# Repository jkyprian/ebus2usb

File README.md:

# ebus2usb - 1TE DIN Rail eBUS to USB Type-C Interface

eBUS is a serial 2-wire serial data-bus, often used in heating, solar energy, and other building automation systems. This project provides an interface to access an eBUS via USB.
It uses a series transistor regulator circuit with a low IZT zener diode to extract the operating voltage from the eBUS, an ADuM1201 for the galvanic isolation, and a STM32 microcontroller for the UART to USB conversion.
Power consumption on the eBUS side is between 475uA (eBUS low/8V) and 750uA (eBUS idle high/24V), making the interface qualify as a class 0 device with respect to the eBUS specification.
It has been designed to fit into an [CNMB/1/2](https://www.camdenboss.com/camden-boss/cnmb12-din-rail-module-box%2c-polycarbonate-enclosure%2c-industrial-iot-electronics-housing/c-23/p-18541) 1TE DIN rail enclosure by CAMDENBOSS. The interface is intended to be used with [ebusd](https://github.com/john30/ebusd/). Note that the firmware is currently just a proof-of-concept and only implements a basic uart to USB bridge. Support for the ebusd enhanced protocol is planned for the near future.

## Schematic

## PCB Layout

When ordering at JLCPCB, remove the mouse bites and cut the boards yourself. Otherwise JLCPCB will charge you for two designs.

## BOM

|Designator|Footprint|Quantity|Value|LCSC Part #
|:---|:---|:---|:---|:---
|C1, C2, C7|C0805|3|10u|C15850
|C10, C3, C4, C5, C6, C8, C9|C0603|7|100n|C14663
|C11, C12|C0805|2|1u|C28323
|D1, D2, D4|SOT-23-3|3|BAV99|C2500
|D3|SOD-123|1|5V6, Onsemi MMSZ4690*|C152307
|D5|SOD-123|1|24V/1W, KDZVTR24B, MM1W24|C209605, C438336
|D6|SOD-123|1|7V5/1W, KDZVTR7.5B, MM1W7V5|C209594, C382950
|D7|LED_0603|1|LED|C72043
|D8, D9, D10|D3.0mm|3|3mm LED|[CHANZON 3mm diffused LED](https://www.aliexpress.com/item/1936229691.html)
|J1|MSTBA_2,5_2-G-5,08|1|MSTBA 2,5/2-G-5,08|C3697
|J2, J6|Molex_PicoBlade_53047-0210|2|Molex 53047-0210|C114130
|J3, J7|Molex_PicoBlade_53047-0410|2|Molex 53047-0410|C504989
|J4|TC2030-NL|1|Tag-Connect 6-Pin \"No Legs\" TC2030-NL Plug-of-Nails|[TC2030-CTX-NL-STDC14](https://www.tag-connect.com/product/tc2030-ctx-nl-stdc14-for-use-with-stm32-processors-with-stlink-v3)
|J5|HRO_TYPE-C-31-M-12|1|HRO TYPE-C-31-M-12|C165948
|J8|PinHeader_1x02_P1.27mm|1|Harwin M50-3530242|C2881948
|Q1, Q2|SOT-23-3|2|BC817-40, S9013J3|C52801, C6749
|R1, R2, R3|R0603|3|100K|C25803
|R10|R0603|1|47K|C25819
|R12, R13|R0603|2|5K1|C23186
|R14|R0805|1|100K|C149504
|R15, R16|R0805|2|15K|C17475
|R4|R0603|1|4K7|C23162
|R5|R0603|1|300K|C23024
|R6|R0603|1|51K|C23196
|R7|R0603|1|2M|C22976
|R8|R0603|1|10K|C25804
|R9|R0603|1|0R|C21189
|U1|SO08|1|AZV3002, TSX3702|C5123396, C2970396
|U2|SO08|1|ADuM1201, π122U31|C9669, C471590
|U5|SOT-23-6L|1|SRV05-4|C85364
|U6|SOT-23-3|1|XC6206P332MR|C5446
|U7|LQFP-32|1|STM32L412KBT6, STM32F042K6T6|C529438, C69216

\* Low IZT of 50uA is required. Other manufacturers than Onsemi may not qualify. For example, MMSZ4690 from Jiangsu Changjing Elec. Tech. is not recommened.

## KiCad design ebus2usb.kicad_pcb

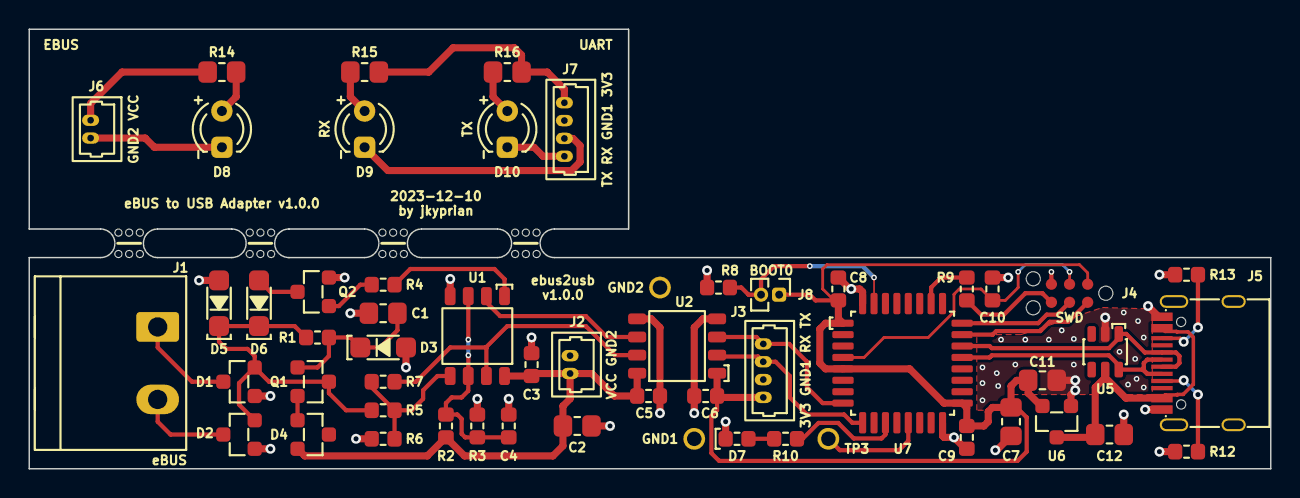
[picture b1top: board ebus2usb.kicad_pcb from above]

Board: 2 copper layers, 87.0 x 30.8 mm, 59 parts (0 on the bottom side), 40 nets.

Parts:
C1, C2, C7: 10u; C0805
C3, C4, C5, C6, C8, C9, C10: 100n; C0603
C11, C12: 1u; C0805
D1, D2, D4: BAV99; SOT-23-3
D3: 5V6; SOD-123
D5: 24V/1W; SOD-123
D6: 7V5/1W; SOD-123
D7: LED; LED_0603
D8, D9, D10: LED; LED_D3.0mm
J1: MSTBA 2,5/2-G-5,08; MSTBA_2,5_2-G-5,08
J2, J6: Molex 53047-0210; Molex_PicoBlade_53047-0210
J3, J7: Molex 53047-0410; Molex_PicoBlade_53047-0410
J4: TC2030; TC-2030NL
J5: HRO TYPE-C-31-M-12; HRO_TYPE-C-31-M-12
J8: Harwin M50-3530242; PinHeader_1x02_P1.27mm
Q1, Q2: BC817-40; SOT-23-3
R1, R2, R3: 100K; R0603
R4: 4K7; R0603
R5: 300K; R0603
R6: 51K; R0603
R7: 2M; R0603
R8: 10K; R0603
R9: 0R; R0603
R10: 47K; R0603
R12, R13: 5K1; R0603
R14: 100K; R0805
R15, R16: 15K; R0805
TP1, TP2, TP3: Keystone 5021; Keystone_5021
U1: AZV3002; SO08
U2: ADuM1201; SO08
U5: SRV05-4; SOT-23-6L
U6: XC6206P332MR; SOT-23-3
U7: STM32L412KBT6; LQFP-32
mouse-bite-2mm-slot, mouse-bite-2mm-slot#2, mouse-bite-2mm-slot#3, mouse-bite-2mm-slot#4: VAL**; mouse-bite-2mm-slot

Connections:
/3V3: C6.2, C7.1, C8.1, C9.1, C11.1, J3.4, J4.1 (VTref), J8.1, U2.1 (VDD1), U6.2 (VO), U7.1 (VDD), U7.5 (VDDA), U7.17 (VDD)
/5V: C12.1, J5.A4 (VBUS), J5.A9 (VBUS), J5.B4 (VBUS), J5.B9 (VBUS), U5.5 (VCC), U6.3 (VI)
/BOOT0: J8.2, R8.2, U7.31 (PH3)
/D+: J5.A6 (D+), J5.B6 (D+), U5.1 (IO1), U7.22 (PA12)
/D-: J5.A7 (D-), J5.B7 (D-), U5.6 (IO4), U7.21 (PA11)
/EBUS: D1.2 (A), D2.2 (A), D5.1 (K), D6.1 (K), Q1.3 (C), R1.2, R5.2
/LED_GREEN: R10.2, U7.11 (PA5)
/NRST: C10.1, J4.3 (NRST), U7.4 (NRST)
/PB3: R9.1, U7.26 (PB3)
/REF: C4.1, R2.1, R3.2, U1.3 (+), U1.6 (-)
/RXD2: J3.2, U2.2 (VOA), U7.9 (PA3)
/SWCLK: J4.4 (SWDCLK/TCK), U7.24 (PA14)
/SWDIO: J4.2 (SWDIO/TMS), U7.23 (PA13)
/SWO: J4.6 (SWO/TDO), R9.2
/TXD2: J3.1, U2.3 (VIB), U7.8 (PA2)
/VCC: C2.1, C3.1, C5.2, D4.2 (A), J2.2, R2.2, U1.8 (V+), U2.8 (VDD2)
/VIA: R7.2, U1.7, U2.7 (VIA)
/VOB: U1.2 (-), U2.6 (VOB)
/_3V3: J7.1, R15.2, R16.2
/_GND2: D8.1 (K), J6.2
/_RXD: D9.1 (K), J7.3
/_TXD: D10.1 (K), J7.4
/_VCC: J6.1, R14.2
GND1: C6.1, C7.2, C8.2, C9.2, C10.2, C11.2, C12.2, D7.1 (K), J3.3, J4.5 (GND), J5.A1 (GND), J5.A12 (GND), J5.B1 (GND), J5.B12 (GND), R8.1, R12.1, R13.1, TP2.1, U2.4 (GND1), U5.2 (GND), U6.1 (GND), U7.16 (VSS), U7.32 (VSS)
GND2: C1.2, C2.2, C3.2, C4.2, C5.1, D1.1 (K), D2.1 (K), D3.2 (A), D5.2 (A), J2.1, Q2.2 (E), R3.1, R6.1, TP1.1, U1.4 (V-), U2.5 (GND2)
unnamed: C1.1, D3.1 (K), Q1.1 (B), R1.1
unnamed: D6.2 (A), Q2.3 (C)
unnamed: D7.2 (A), R10.1
unnamed: D8.2 (A), R14.1
unnamed: D9.2 (A), R15.1
unnamed: D10.2 (A), R16.1
unnamed: D1.3 (K), J1.1
unnamed: D2.3 (K), J1.2
unnamed: J5.A5 (CC1), R12.2
unnamed: J5.B5 (CC2), R13.2
unnamed: D4.1 (K), Q1.2 (E)
unnamed: Q2.1 (B), R4.1
unnamed: R4.2, U1.1
unnamed: R5.1, R6.2, R7.1, U1.5 (+)
unnamed: TP3.1, U7.13 (PA7)

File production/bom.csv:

Designator,Footprint,Quantity,Value,LCSC Part #
"C1, C2, C7",C0805,3,10u,C15850
"C10, C3, C4, C5, C6, C8, C9",C0603,7,100n,C14663
"C11, C12",C0805,2,1u,C28323
"D1, D2, D4",SOT-23-3,3,BAV99,C2500
D3,SOD-123,1,5V6,C152307
D5,SOD-123,1,24V/1W,C209605
D6,SOD-123,1,7V5/1W,C209594
D7,LED_0603,1,LED,C72043
J1,"MSTBA_2,5_2-G-5,08",1,"MSTBA 2,5/2-G-5,08",C3697
"J2, J6",Molex_PicoBlade_53047-0210,2,Molex 53047-0210,C114130
"J3, J7",Molex_PicoBlade_53047-0410,2,Molex 53047-0410,C504989
J5,HRO_TYPE-C-31-M-12,1,HRO TYPE-C-31-M-12,C165948
J8,PinHeader_1x02_P1.27mm,1,Harwin M50-3530242,C2881948
"Q1, Q2",SOT-23-3,2,BC817-40,C6749
"R1, R2, R3",R0603,3,100K,C25803
R10,R0603,1,47K,C25819
"R12, R13",R0603,2,5K1,C23186
R14,R0805,1,100K,C149504
"R15, R16",R0805,2,15K,C17475
R4,R0603,1,4K7,C23162
R5,R0603,1,300K,C23024
R6,R0603,1,51K,C23196
R7,R0603,1,2M,C22976
R8,R0603,1,10K,C25804
R9,R0603,1,0R,C21189
U1,SO08,1,AZV3002,C5123396
U2,SO08,1,ADuM1201,C9669
U5,SOT-23-6L,1,SRV05-4,C85364
U6,SOT-23-3,1,XC6206P332MR,C5446
U7,LQFP-32,1,STM32L412KBT6,C529438

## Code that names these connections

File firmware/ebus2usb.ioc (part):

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Mcu.Name=STM32L412KBTx
Mcu.Package=LQFP32
Mcu.UserName=STM32L412KBTx
PA11.Mode=Device
PA11.Signal=USB_DM
PA12.Mode=Device
PA12.Signal=USB_DP
PA13\ (JTMS/SWDIO).Mode=Trace_Asynchronous_SW
PA13\ (JTMS/SWDIO).Signal=SYS_JTMS-SWDIO
PA14\ (JTCK/SWCLK).Mode=Trace_Asynchronous_SW
PA14\ (JTCK/SWCLK).Signal=SYS_JTCK-SWCLK
PA2.Mode=Asynchronous
PA2.Signal=USART2_TX
PA3.Mode=Asynchronous
PA3.Signal=USART2_RX
PA5.GPIOParameters=GPIO_Label
PA5.GPIO_Label=LED
PA5.Signal=GPIO_Output
PA7.GPIOParameters=GPIO_Label
PA7.GPIO_Label=TP3
PA7.Signal=GPIO_Output
PB3\ (JTDO/TRACESWO).Mode=Trace_Asynchronous_SW
PB3\ (JTDO/TRACESWO).Signal=SYS_JTDO-SWO
RCC.HSE_VALUE=8000000
RCC.SYSCLKFreq_VALUE=80000000
RCC.SYSCLKSource=RCC_SYSCLKSOURCE_PLLCLK
board=custom

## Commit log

2023-05-08 v0.8
2023-05-15 v0.8.1 * Size of main board changed to 87mm x 14.8mm * R5 changed from 1K5 to 4K7 * TS3702/TCL3702 replaced by TSX3702 (need VCC on one input)
2023-07-08 * Replaced voltage reference with low IZT 5V6 zener diode (cheaper but increases power consumption on the eBus side by ~200uA) * C2/C4 changed to 10u * R6/R7 adjusted for ~5V VCC * AZV3002 as replace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
2023-10-10 2TE -> 1TE
2023-12-10 New version with STM32 microcontroller.
2023-12-11 Added info for TC2030-NL to schematic and BOM
